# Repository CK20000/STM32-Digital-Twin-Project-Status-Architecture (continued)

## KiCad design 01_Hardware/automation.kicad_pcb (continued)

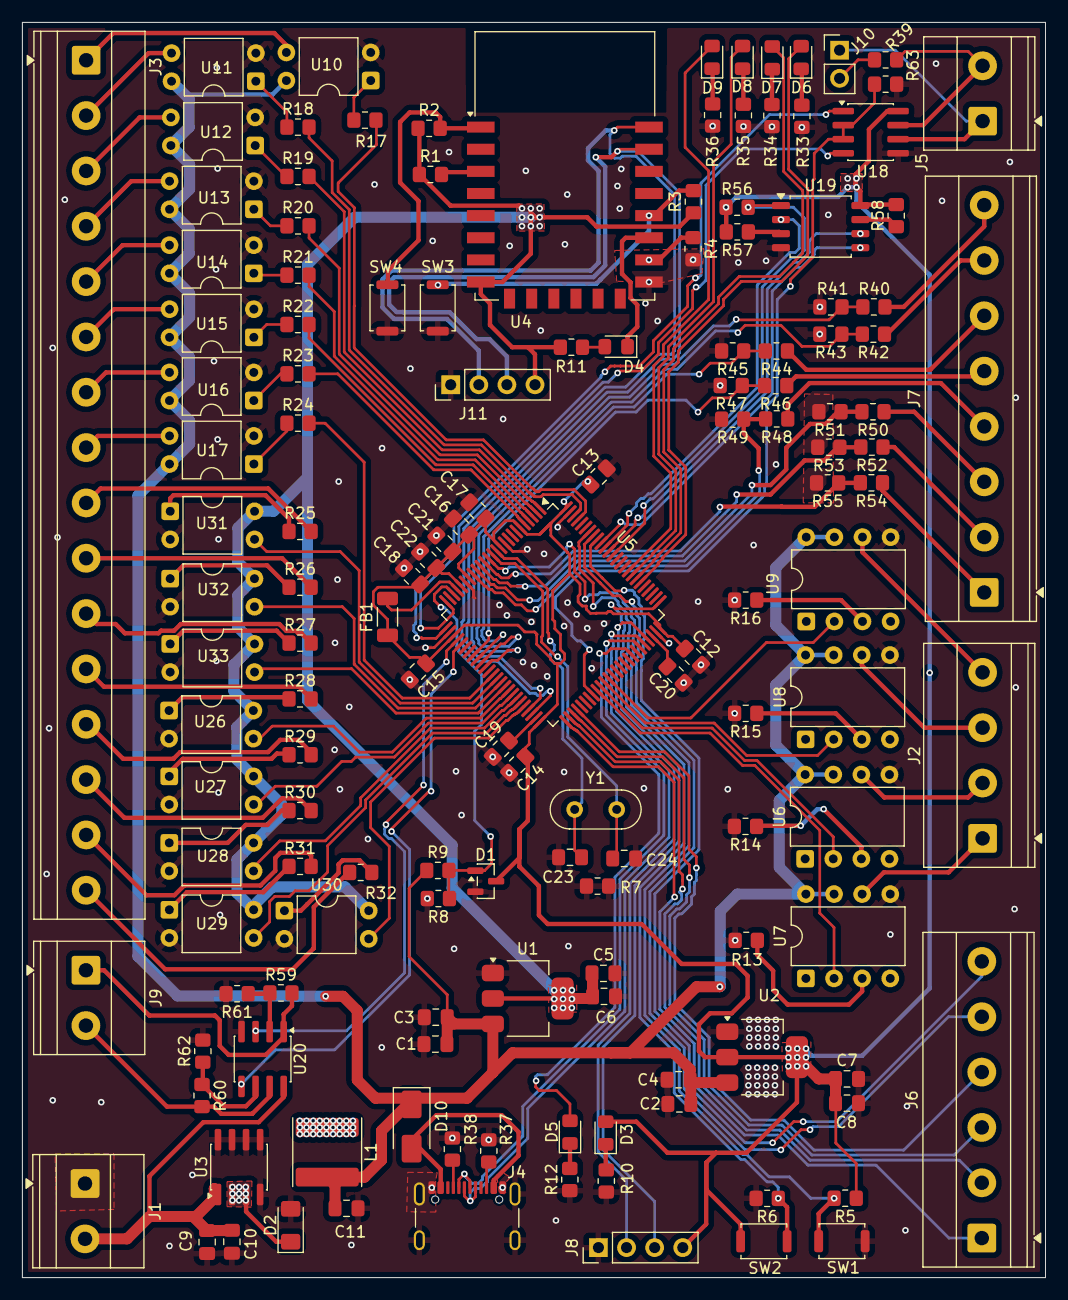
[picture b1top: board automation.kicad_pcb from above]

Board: 2 copper layers, 92.4 x 113.4 mm, 143 parts (0 on the bottom side), 140 nets.

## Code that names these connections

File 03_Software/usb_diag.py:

"""
usb_diag.py — one-shot register probe against a running Renode instance.

Prereq: Renode is listening on 127.0.0.1:1234
        (run_core.bat, or: renode --port 1234 machine.resc)

Reads:
  RCC_AHB2ENR   0x40023834   bit 7 = OTG_FSEN  (set by HAL_PCD_MspInit)
  GPIOA_MODER   0x40020000   PA mode
  GPIOA_AFRH    0x40020024   PA8..PA15 alternate function
  GPIOD_MODER   0x40020C02   PD8..PD15 mode  (firmware drives PD12..PD15)
  GPIOE_MODER   0x40021000   PE0..PE7   mode  (firmware drives all of PE0..PE7)
  SYSCFG_MEMRMP 0x40013800   boot mode

Usage:
    python usb_diag.py
    python usb_diag.py --raw    # also dump each raw monitor reply
"""
import argparse
import re
import socket
import sys
import time

RENODE_HOST = "127.0.0.1"
RENODE_PORT = 1234

ANSI_RE     = re.compile(r"\x1b\[[0-9;?]*[A-Za-z]")
TELNET_CMDS = (0xFB, 0xFC, 0xFD, 0xFE)
PROMPT_RE   = re.compile(r"\(([A-Za-z0-9_\-\.]+)\)\s*$", re.MULTILINE)


def clean(raw: bytes) -> str:
    out = bytearray()
    i = 0
    while i < len(raw):
        b = raw[i]
        if b == 0xFF and i + 1 < len(raw):
            nxt = raw[i + 1]
            if nxt in TELNET_CMDS and i + 2 < len(raw):
                i += 3
                continue
            if nxt == 0xFF:
                out.append(0xFF)
                i += 2
                continue
            i += 2
            continue
        out.append(b)
        i += 1
    return ANSI_RE.sub("", out.decode("ascii", errors="replace")).replace("\r", "")


class Monitor:
    def __init__(self, host, port, debug=False):
        self.debug = debug
        self.sock = socket.create_connection((host, port), timeout=5.0)
        self.sock.settimeout(0.25)
        self.buf = bytearray()
        self.prompt = None

        # Drain any greeting Renode sends on connect
        time.sleep(0.3)
        try:
            self.sock.recv(4096)
        except socket.timeout:
            pass
        self.buf.clear()

        # Renode does not emit its prompt until it sees a newline.
        # Send a blank line, then wait for the prompt to appear.
        self._send("")

        deadline = time.time() + 4.0
        while time.time() < deadline:
            try:
                chunk = self.sock.recv(4096)
                if chunk:
                    self.buf.extend(chunk)
            except socket.timeout:
                pass

            text = clean(self.buf)
            if self.debug:
                print(f"    [handshake] buf so far: {text[-120:]!r}")

            # Preferred: a line ending with "(name) " — our strict pattern
            matches = PROMPT_RE.findall(text)
            if matches:
                self.prompt = f"({matches[-1]}) "
                idx = text.rfind(self.prompt)
                self.buf = bytearray(
                    text[idx + len(self.prompt):].encode("ascii", errors="ignore"))
                return

            # Fallback: any "(something)" at end of a line
            m = re.search(r"\(([^)\r\n]+)\)\s*$", text, re.MULTILINE)
            if m:
                self.prompt = m.group(0)  # includes the trailing spaces
                idx = text.rfind(self.prompt)
                self.buf = bytearray(
                    text[idx + len(self.prompt):].encode("ascii", errors="ignore"))
                return

        # Still nothing? Use the same default renode_reader.py uses.
        print("[!] No prompt detected. Falling back to '(plc_twin) '")
        self.prompt = "(plc_twin) "

    def _send(self, cmd):
        self.sock.sendall((cmd + "\n").encode("ascii"))

    def _read(self, timeout_s=2.0):
        deadline = time.time() + timeout_s
        while time.time() < deadline:
            text = clean(self.buf)
            if self.prompt:
                idx = text.rfind(self.prompt)
                if idx >= 0:
                    payload = text[:idx]
                    self.buf = bytearray(
                        text[idx + len(self.prompt):].encode("ascii", errors="ignore"))
                    return payload
            try:
                chunk = self.sock.recv(4096)
                if not chunk:
                    raise ConnectionError("monitor closed")
                self.buf.extend(chunk)
            except socket.timeout:
                continue
        text = clean(self.buf)
        if self.debug:
            print(f"    [read] timed out, buf = {text[-200:]!r}")
        return text

    def read_word(self, addr):
        self._send(f"sysbus ReadWord 0x{addr:08X}")
        raw = self._read()
        if self.debug:
            print(f"    [raw] ReadWord 0x{addr:08X} -> {raw.strip()!r}")
        toks = re.findall(r"0x([0-9a-fA-F]+)", raw)
        if not toks:
            raise ValueError(f"no hex token in reply: {raw!r}")
        return int(toks[-1], 16)

    def close(self):
        try:
            self.sock.close()
        except Exception:
            pass


def main():
    ap = argparse.ArgumentParser()
    ap.add_argument("--raw", action="store_true", help="dump raw monitor replies")
    args = ap.parse_args()

    print(f"[*] Connecting to Renode monitor {RENODE_HOST}:{RENODE_PORT} ...")
    try:
        mon = Monitor(RENODE_HOST, RENODE_PORT, debug=args.raw)
    except Exception as e:
        print(f"[!] Connection failed: {type(e).__name__}: {e}")
        print("[!] Is Renode running? Try: run_core.bat")
        sys.exit(1)
    print(f"[*] Connected.  Prompt = {mon.prompt!r}")
    print()

    # --- 1. RCC_AHB2ENR.bit7 ---
    ahb2enr = mon.read_word(0x40023834)
    otg_fs_en = (ahb2enr >> 7) & 1
    print(f"RCC_AHB2ENR     = 0x{ahb2enr:08X}   OTG_FSEN = {otg_fs_en}")

    # --- 2. GPIOA MODER (Renode ReadWord is 16-bit; PA0..PA7 at +0x00, PA8..PA15 at +0x02) ---
    ga_lo = mon.read_word(0x40020000)
    ga_hi = mon.read_word(0x40020002)
    pa11_mode = (ga_hi >> ((11 - 8) * 2)) & 0x3
    pa12_mode = (ga_hi >> ((12 - 8) * 2)) & 0x3
    print(f"GPIOA_MODER_lo  = 0x{ga_lo:04X}                (PA0..PA7)")
    print(f"GPIOA_MODER_hi  = 0x{ga_hi:04X}                PA11_mode={pa11_mode}  PA12_mode={pa12_mode}")

    # --- 3. GPIOA AFRH ---
    afrh = mon.read_word(0x40020024)
    pa11_af = (afrh >> ((11 - 8) * 4)) & 0xF
    pa12_af = (afrh >> ((12 - 8) * 4)) & 0xF
    print(f"GPIOA_AFRH      = 0x{afrh:04X}                PA11_AF={pa11_af}  PA12_AF={pa12_af}")

    # --- 4. GPIOD MODER_hi (PD8..PD15) ---
    gd_hi = mon.read_word(0x40020C02)
    pd12_mode = (gd_hi >> ((12 - 8) * 2)) & 0x3
    pd13_mode = (gd_hi >> ((13 - 8) * 2)) & 0x3
    pd14_mode = (gd_hi >> ((14 - 8) * 2)) & 0x3
    pd15_mode = (gd_hi >> ((15 - 8) * 2)) & 0x3
    print(f"GPIOD_MODER_hi  = 0x{gd_hi:04X}                "
          f"PD12={pd12_mode} PD13={pd13_mode} PD14={pd14_mode} PD15={pd15_mode}")

    # --- 5. GPIOE MODER_lo (PE0..PE7) ---
    ge_lo = mon.read_word(0x40021000)
    print(f"GPIOE_MODER_lo  = 0x{ge_lo:04X}                (want 0x5555)")

    # --- 6. SYSCFG_MEMRMP ---
    memrmp = mon.read_word(0x40013800)
    print(f"SYSCFG_MEMRMP   = 0x{memrmp:04X}                MEM_MODE={memrmp & 0x7}")

    mon.close()
    print()
    print("=" * 66)
    print("INTERPRETATION")
    print("=" * 66)

    pa_mux_ok = (pa11_mode == 2 and pa12_mode == 2
                 and pa11_af == 10 and pa12_af == 10)
    other_gpio_ok = (ge_lo == 0x5555) or (gd_hi != 0)

    if otg_fs_en == 1:
        print("OTG_FSEN = 1  →  HAL_PCD_MspInit() ran.")
        if pa_mux_ok:
            print("PA11/PA12 = AF10  →  USB pins are correctly muxed.")
            print()
            print("→ Firmware is fine. The earlier 'MODER=0 AF=0' reading")
            print("  was a script bug (reading only the low half of MODER).")
        else:
            print(f"PA11/PA12 NOT AF10 (got {pa11_mode}/{pa11_af} and "
                  f"{pa12_mode}/{pa12_af})  →  MspInit ran but did not mux USB.")
            print()
            print("→ Check usb_device.c / usbd_conf.c HAL_PCD_MspInit() body.")
    else:
        print("OTG_FSEN = 0  →  HAL_PCD_MspInit() did NOT run.")
        if other_gpio_ok:
            print("But PE0..PE7 / PD12..PD15 ARE configured → GPIO writes persist")
            print("in Renode, so this is a genuine firmware gap, not a Renode")
            print("model issue.")
            print()
            print("→ MX_USB_DEVICE_Init() bailed before reaching HAL_PCD_MspInit().")
            print("  Next: grep firmware/ for MX_USB_DEVICE_Init / HAL_PCD_MspInit /")
            print("  USBD_LL_Init to see where it returns early.")
        else:
            print("And PE0..PE7 / PD12..PD15 are ALSO unconfigured in Renode.")
            print()
            print("→ Renode's STM32F4 GPIO model may not persist MODER/AFR writes")
            print("  at all. If so, the pin-mux check is meaningless in the twin")
            print("  and must move to post-fab hardware verification only.")
    print()


if __name__ == "__main__":
    main()

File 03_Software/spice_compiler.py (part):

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
def emit_industrial_drivers(pin_map):
    """V-sources on the MCU pins that drive industrial output optos
    (PE0..PE7) and motor optos (PD12..PD15). Firmware-controlled."""
    lines = []
    u5_pins = pin_map.get("U5", {})
    PIN_MAP = {
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

def emit_dac_sources(netlist):
    """STM32 DAC pins drive daq1 and daq2. Firmware controls them;
    for now, park them at 0.5 V (solver overrides per packet)."""
    lines = ["* === DAC sources ==="]
    for net_name in ("daq1", "daq2"):
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
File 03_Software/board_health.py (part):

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    # --- D+/D- to MCU ---
    dp = pins_on("USB.D+", "U5")
    dm = pins_on("USB.D-", "U5")
    out.append(("USB D+ → PA12",
                "PASS" if "71" in dp else "FAIL",
                "U5 pin 71" if "71" in dp else f"pins={dp}"))
    out.append(("USB D- → PA11",
                "PASS" if "70" in dm else "FAIL",
                "U5 pin 70" if "70" in dm else f"pins={dm}"))

    # --- VBUS sense (PA9) ---
    pa9_nets = [n for n, d in nl.items() for x in d.get("nodes", [])
                if x["component"] == "U5" and x["pin"] == "68"]
    if pa9_nets and "usb_led" in pa9_nets[0].lower():
        out.append(("USB VBUS sense", "WARN",
                    "PA9→usb_led; firmware MUST set vbus_sensing_enable=0"))
    elif pa9_nets:
        out.append(("USB VBUS sense", "PASS", f"PA9 on {pa9_nets[0]}"))
    else:
        out.append(("USB VBUS sense", "WARN", "PA9 not connected"))

    # --- BOOT0 strap (DFU entry) ---
    b = nodes("boot0")
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    for label, status, detail in state.get("usb_topology", []):
        rows.append((label, (status, detail)))

    # PA11/PA12 mux — from the one-shot register snapshot
    with lock:
        regs = dict(state["usbreg"])
    moder_e = regs.get("GPIOA_MODER")
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        afrh  = afrh_e[0]
        pa11_mode = (moder >> 22) & 0x3
        pa12_mode = (moder >> 24) & 0x3
        pa11_af   = (afrh  >> 12) & 0xF   # PA11: bits 12..15 of AFRH
        pa12_af   = (afrh  >> 16) & 0xF   # PA12: bits 16..19 of AFRH
        rows.append(("USB PA11 mux",
            ("PASS" if (pa11_mode == 2 and pa11_af == 10) else "FAIL",
             f"MODER={pa11_mode} AF={pa11_af} (want 2/10)")))
        rows.append(("USB PA12 mux",
            ("PASS" if (pa12_mode == 2 and pa12_af == 10) else "FAIL",
             f"MODER={pa12_mode} AF={pa12_af} (want 2/10)")))

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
